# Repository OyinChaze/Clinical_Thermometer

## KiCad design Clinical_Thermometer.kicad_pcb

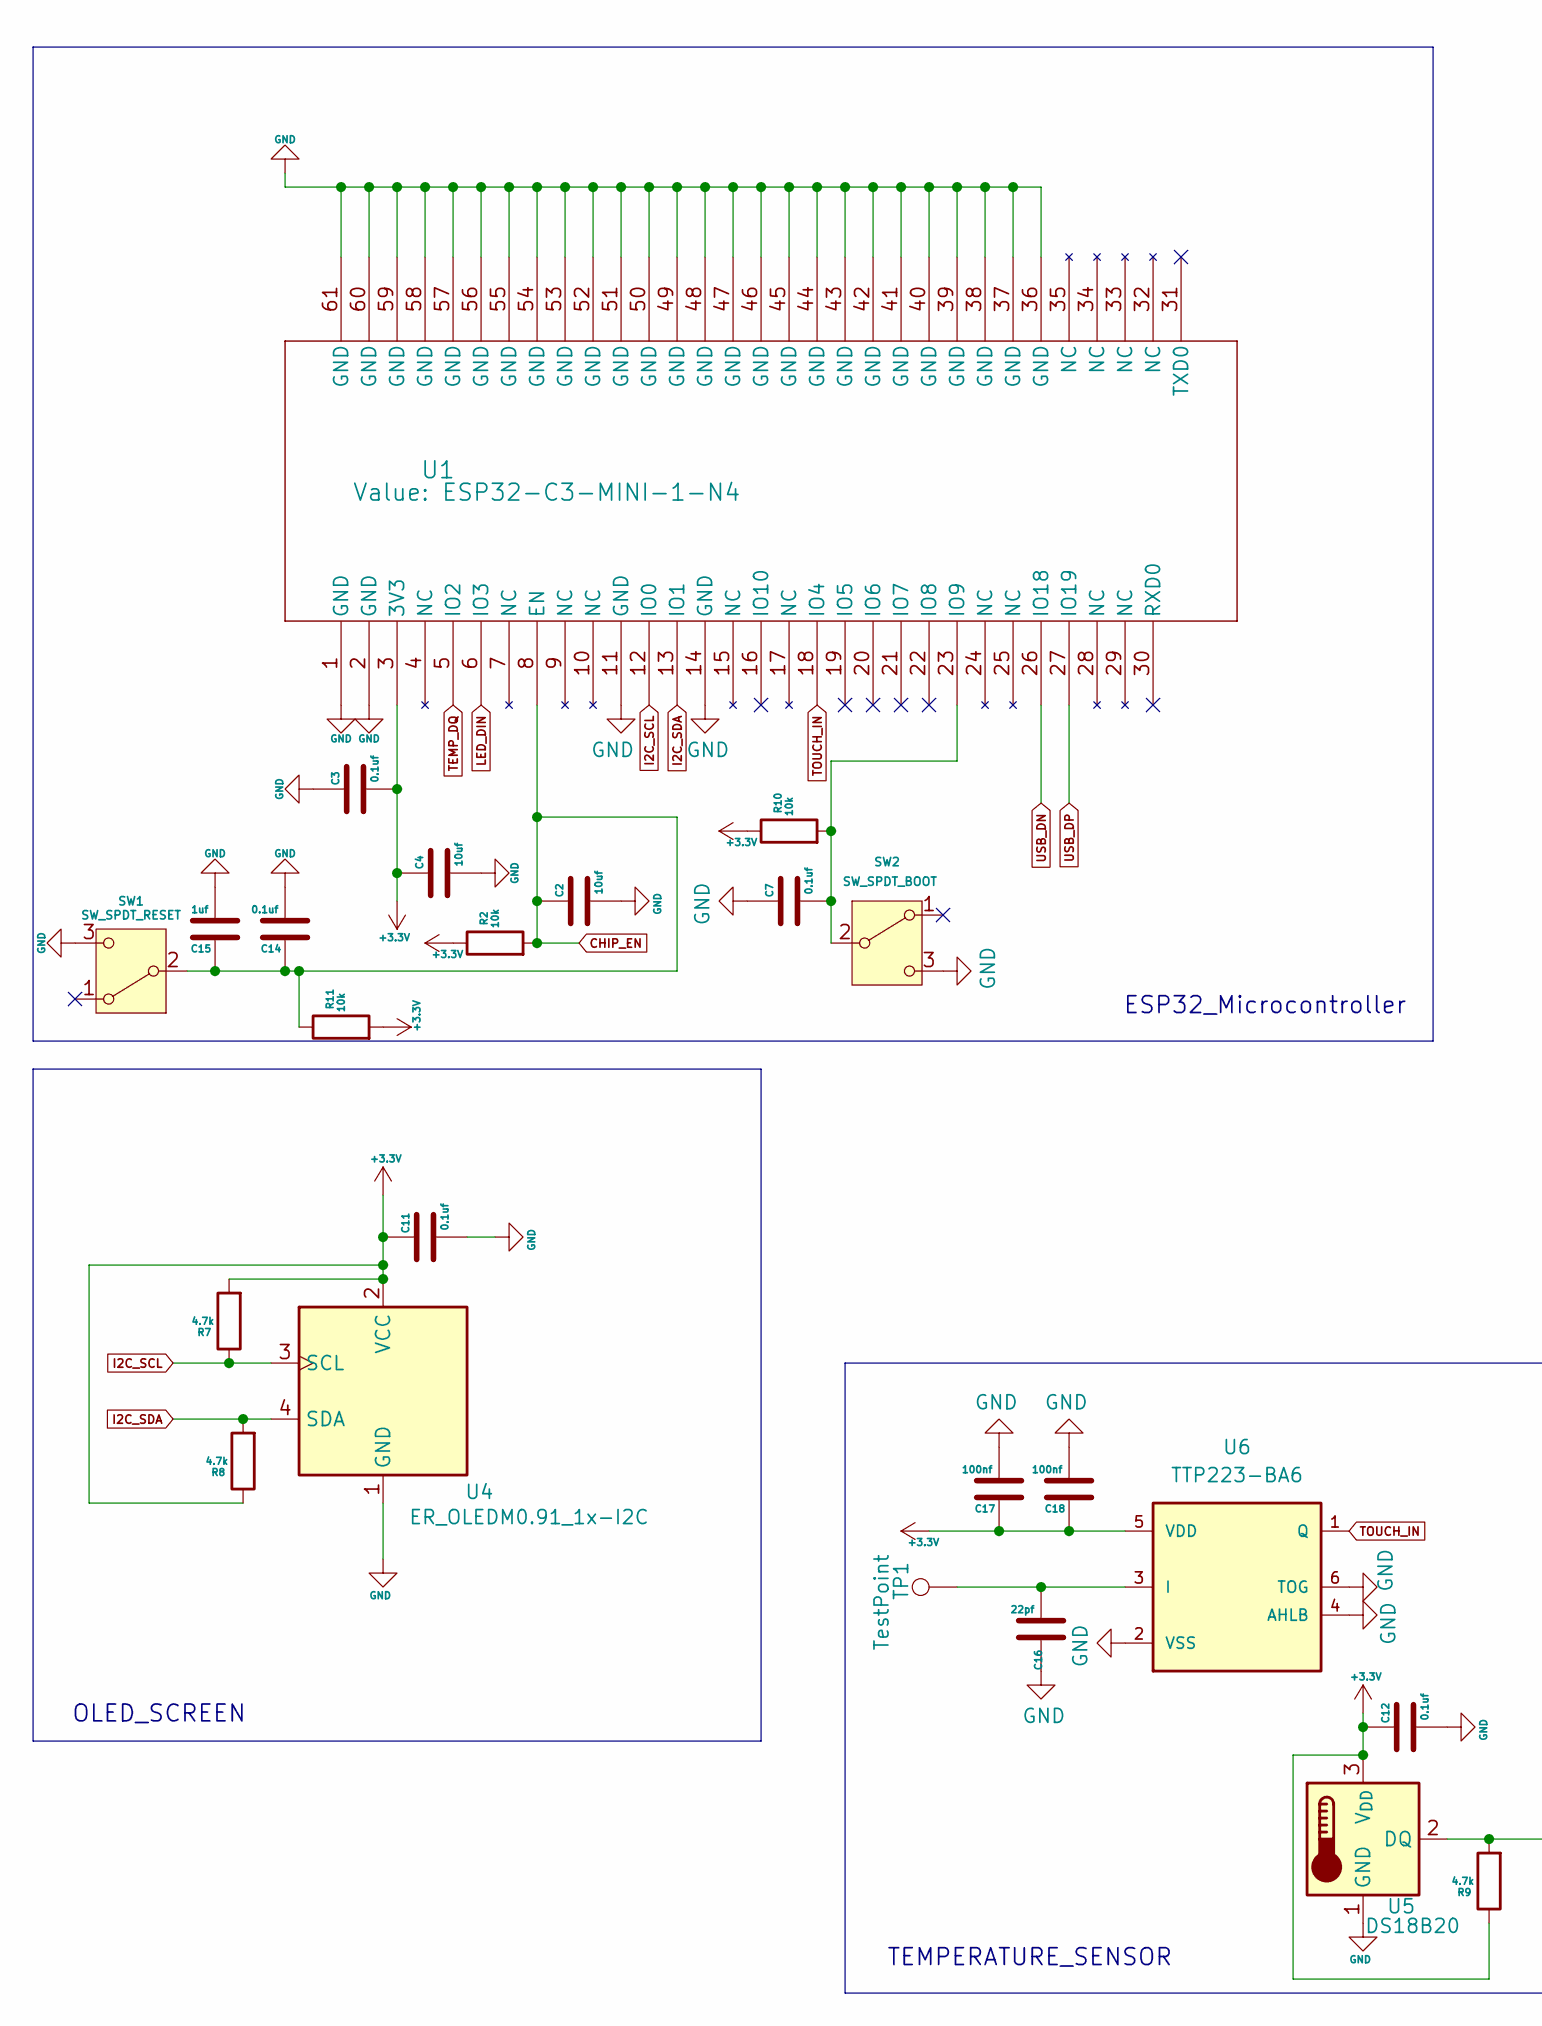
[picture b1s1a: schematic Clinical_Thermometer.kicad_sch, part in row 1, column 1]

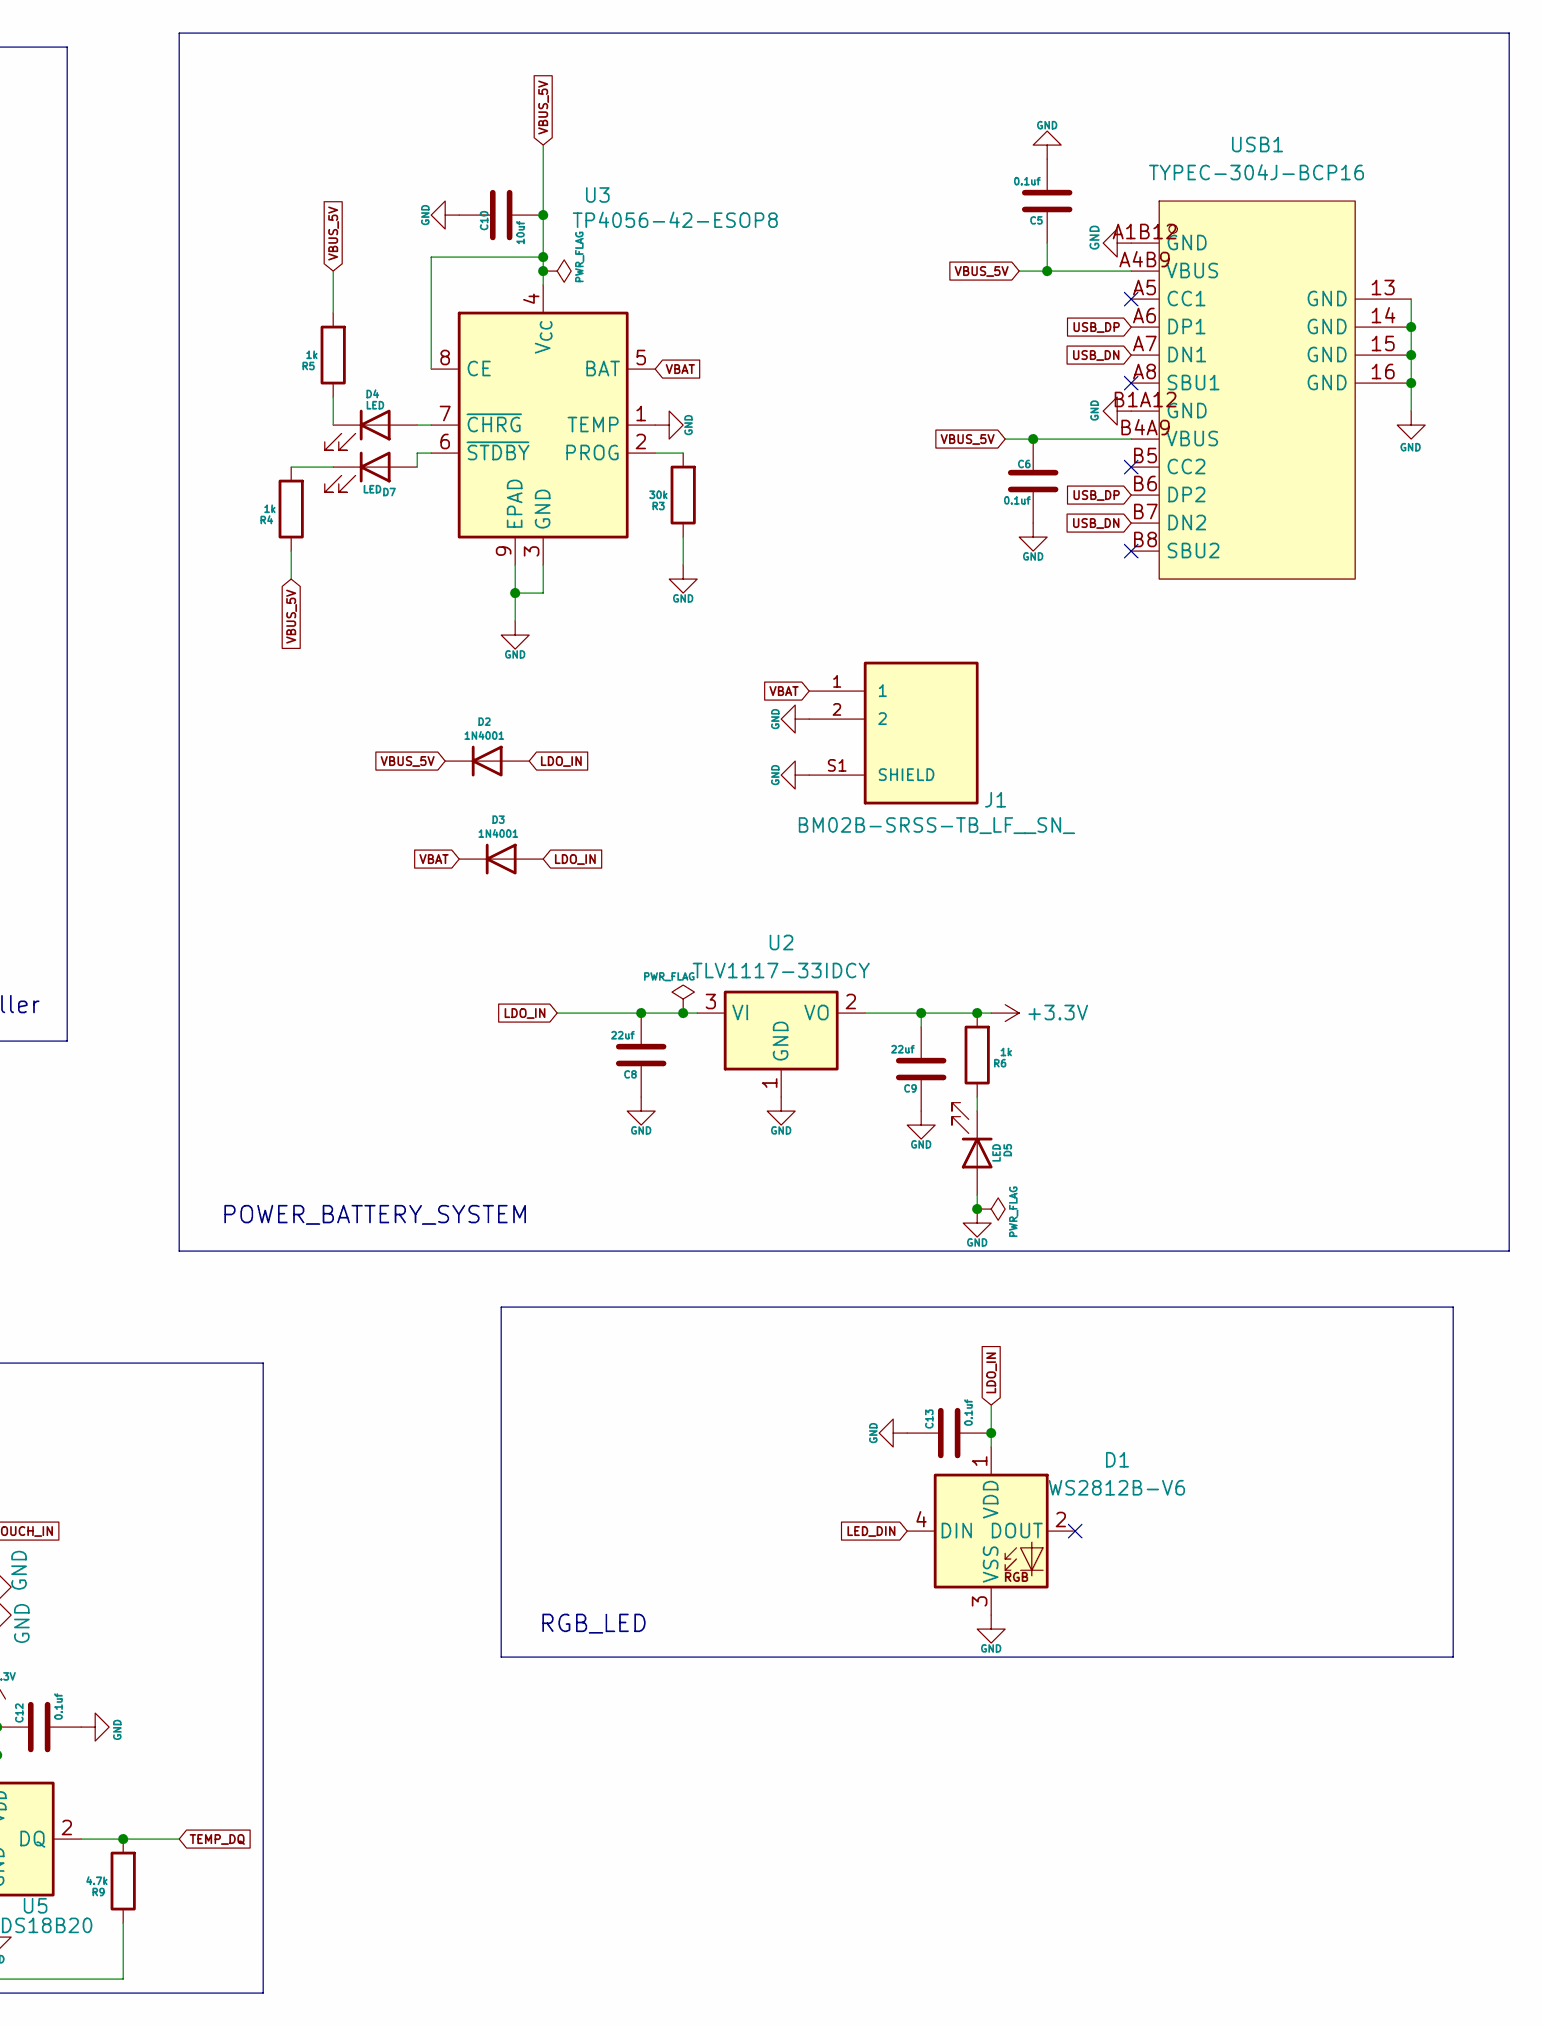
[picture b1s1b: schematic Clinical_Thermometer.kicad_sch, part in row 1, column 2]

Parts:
C2, C4, C10: 10uf; C_0402_1005Metric; LCSC Part C315248
C3, C5, C6, C7, C11, C12, C13, C14: 0.1uf; C_0402_1005Metric; LCSC Part C131394
C8, C9: 22uf; C_0402_1005Metric; LCSC Part C3854737
C15: 1uf; C_0402_1005Metric; LCSC Part C29266
C16: 22pf; C_0402_1005Metric; LCSC Part C2168192
C17, C18: 100nf; C_0402_1005Metric; LCSC Part C60474
D1: WS2812B-V6; LED_WS2812B_PLCC4_5.0x5.0mm_P3.2mm; LCSC Part C52917433
D2, D3: 1N4001; D_0402_1005Metric; LCSC Part C145305
D4, D5, D7: LED; LED_0402_1005Metric; LCSC Part C74338
J1: BM02B-SRSS-TB_LF__SN_; JST_BM02B-SRSS-TB_LF__SN_; PARTREV N/A; LCSC Part C160388
R2, R10, R11: 10k; R_0402_1005Metric; LCSC Part C60490
R3: 30k; R_0402_1005Metric; LCSC Part C138008
R4, R5, R6: 1k; R_0402_1005Metric; LCSC Part C106235
R7, R8, R9: 4.7k; R_0402_1005Metric; LCSC Part C105871
SW1: SW_SPDT_RESET; PTS636SM25FSMTRLFS; LCSC Part C2800443
SW2: SW_SPDT_BOOT; PTS636SM25FSMTRLFS; LCSC Part C2800443
TP1: TestPoint; TestPoint_Pad_1.0x1.0mm
U1: ESP32-C3-MINI-1-N4; ESP32-C3-MINI-1_EXP; LCSC Part C2838502
U2: TLV1117-33IDCY; SOT-223-3_TabPin2; LCSC Part C2877971
U3: TP4056-42-ESOP8; SOIC-8-1EP_3.9x4.9mm_P1.27mm_EP2.41x3.3mm_ThermalVias; LCSC Part C16581
U4: ER_OLEDM0.91_1x-I2C; LCSC Part C5248081
U5: DS18B20; TO-92_Inline
U6: TTP223-BA6; SOT-23-6; LCSC Part C42422127
USB1: TYPEC-304J-BCP16; USB-C-SMD_TYPEC-304J-BCP16; MPN TYPEC-304J-BCP16; LCSC Part C2835315

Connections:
+3.3V: C3.2, C4.1, C9.2, C11.1, C12.1, C17.1, C18.1, R2.1, R6.2, R7.2, R8.1, R9.1, R10.1, R11.2, U1.3 (3V3), U2.2 (VO), U4.2 (VCC), U5.3 (V_{DD}), U6.5 (VDD)
CHIP_EN: C2.1, C14.1, C15.1, R2.2, R11.1, SW1.2 (B_2), U1.8 (EN)
GND: C2.2, C3.1, C4.2, C5.2, C6.2, C7.1, C8.1, C9.1, C10.1, C11.2, C12.2, C13.1, C14.2, C15.2, C16.1, C17.2, C18.2, D1.3 (VSS), D5.2 (A), J1.2, J1.S1 (SHIELD), J1.S2 (SHIELD), R3.1, SW1.3 (C), SW2.3 (C), U1.1 (GND), U1.2 (GND), U1.11 (GND), U1.14 (GND), U1.36 (GND), U1.37 (GND), U1.38 (GND), U1.39 (GND), U1.40 (GND), U1.41 (GND), U1.42 (GND), U1.43 (GND), U1.44 (GND), U1.45 (GND), U1.46 (GND), U1.47 (GND), U1.48 (GND), U1.49 (GND), U1.50 (GND), U1.51 (GND), U1.52 (GND), U1.53 (GND), U1.54 (GND), U1.55 (GND), U1.56 (GND), U1.57 (GND), U1.58 (GND), U1.59 (GND), U1.60 (GND), U1.61 (GND), U2.1 (GND), U3.1 (TEMP), U3.3 (GND), U3.9 (EPAD), U4.1 (GND), U5.1 (GND), U6.2 (VSS), U6.4 (AHLB), U6.6 (TOG), USB1.13 (GND), USB1.14 (GND), USB1.15 (GND), USB1.16 (GND), USB1.A1B12 (GND), USB1.B1A12 (GND)
I2C_SCL: R7.1, U1.12 (IO0), U4.3 (SCL)
I2C_SDA: R8.2, U1.13 (IO1), U4.4 (SDA)
LDO_IN: C8.2, C13.2, D1.1 (VDD), D2.2 (A), D3.2 (A), U2.3 (VI)
LED_DIN: D1.4 (DIN), U1.6 (IO3)
unnamed: D4.2 (A), U3.7 (~CHRG)
unnamed: D4.1 (K), R5.1
unnamed: D5.1 (K), R6.1
unnamed: D7.2 (A), U3.6 (~STDBY)
unnamed: D7.1 (K), R4.2
unnamed: C7.2, R10.2, SW2.2 (B_2), U1.23 (IO9)
unnamed: R3.2, U3.2 (PROG)
unnamed: C16.2, TP1.1 (1_1), U6.3 (I)
TEMP_DQ: R9.2, U1.5 (IO2), U5.2 (DQ)
TOUCH_IN: U1.18 (IO4), U6.1 (Q)
USB_DN: U1.26 (IO18), USB1.A7 (DN1), USB1.B7 (DN2)
USB_DP: U1.27 (IO19), USB1.A6 (DP1), USB1.B6 (DP2)
VBAT: D3.1 (K), J1.1, U3.5 (BAT)
VBUS_5V: C5.1, C6.1, C10.2, D2.1 (K), R4.1, R5.2, U3.4 (V_{CC}), U3.8 (CE), USB1.A4B9 (VBUS), USB1.B4A9 (VBUS)

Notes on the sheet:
TEMPERATURE_SENSOR
RGB_LED
ESP32_Microcontroller
POWER_BATTERY_SYSTEM
OLED_SCREEN

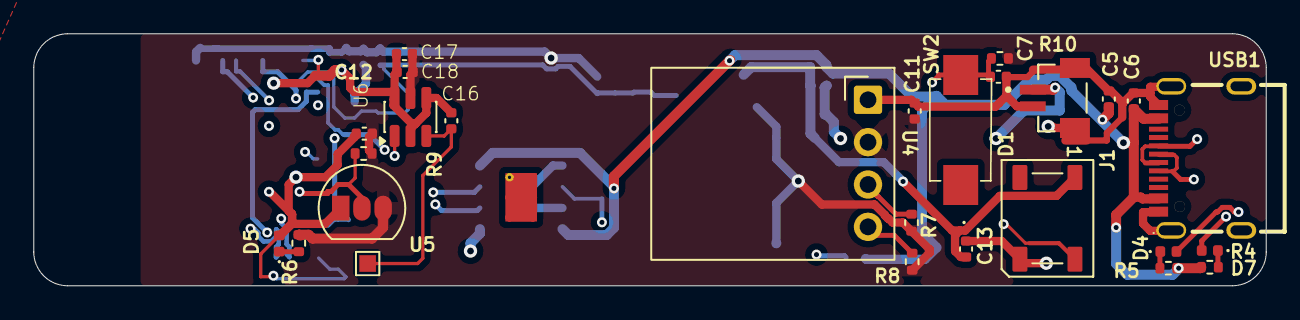
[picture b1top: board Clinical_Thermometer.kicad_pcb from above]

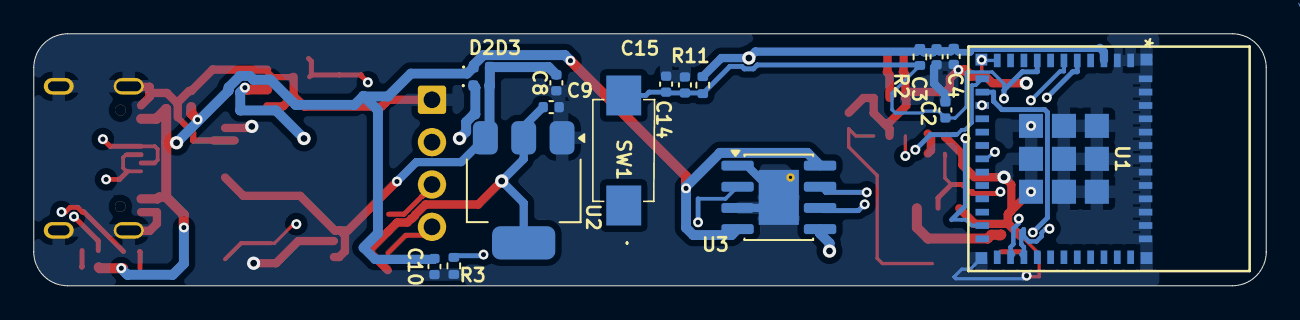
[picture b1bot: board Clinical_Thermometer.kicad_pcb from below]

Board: 4 copper layers, 73.9 x 15.1 mm, 44 parts (17 on the bottom side), 21 nets.

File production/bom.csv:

Designator,Footprint,Quantity,Value,LCSC Part #
"C10, C2, C4",0402,3,10uf,
"C11, C12, C13, C14, C3, C5, C6, C7",0402,8,0.1uf,
C15,0402,1,1uf,
C16,0402,1,22pf,
"C17, C18",0402,2,100nf,
"C8, C9",0402,2,22uf,
D1,LED_WS2812B_PLCC4_5.0x5.0mm_P3.2mm,1,WS2812B-V6,
"D2, D3",0402,2,1N4001,
"D4, D5, D7",0402,3,LED,
J1,JST_BM02B-SRSS-TB_LF__SN_,1,BM02B-SRSS-TB_LF__SN_,
"R10, R11, R2",0402,3,10k,
R3,0402,1,30k,
"R4, R5, R6",0402,3,1k,
"R7, R8, R9",0402,3,4.7k,
SW1,PTS636SM25FSMTRLFS,1,SW_SPDT_RESET,
SW2,PTS636SM25FSMTRLFS,1,SW_SPDT_BOOT,
TP1,TestPoint_Pad_1.0x1.0mm,1,TestPoint,
U1,ESP32-C3-MINI-1_EXP,1,ESP32-C3-MINI-1-N4,
U2,SOT-223-3_TabPin2,1,TLV1117-33IDCY,
U3,SOIC-8-1EP_3.9x4.9mm_P1.27mm_EP2.41x3.3mm_ThermalVias,1,TP4056-42-ESOP8,
U4,ER_OLEDM0.91_1x-I2C,1,ER_OLEDM0.91_1x-I2C,
U5,TO-92_Inline,1,DS18B20,
U6,SOT-23-6,1,TTP223-BA6,
USB1,USB-C-SMD_TYPEC-304J-BCP16,1,TYPEC-304J-BCP16,C2835315
